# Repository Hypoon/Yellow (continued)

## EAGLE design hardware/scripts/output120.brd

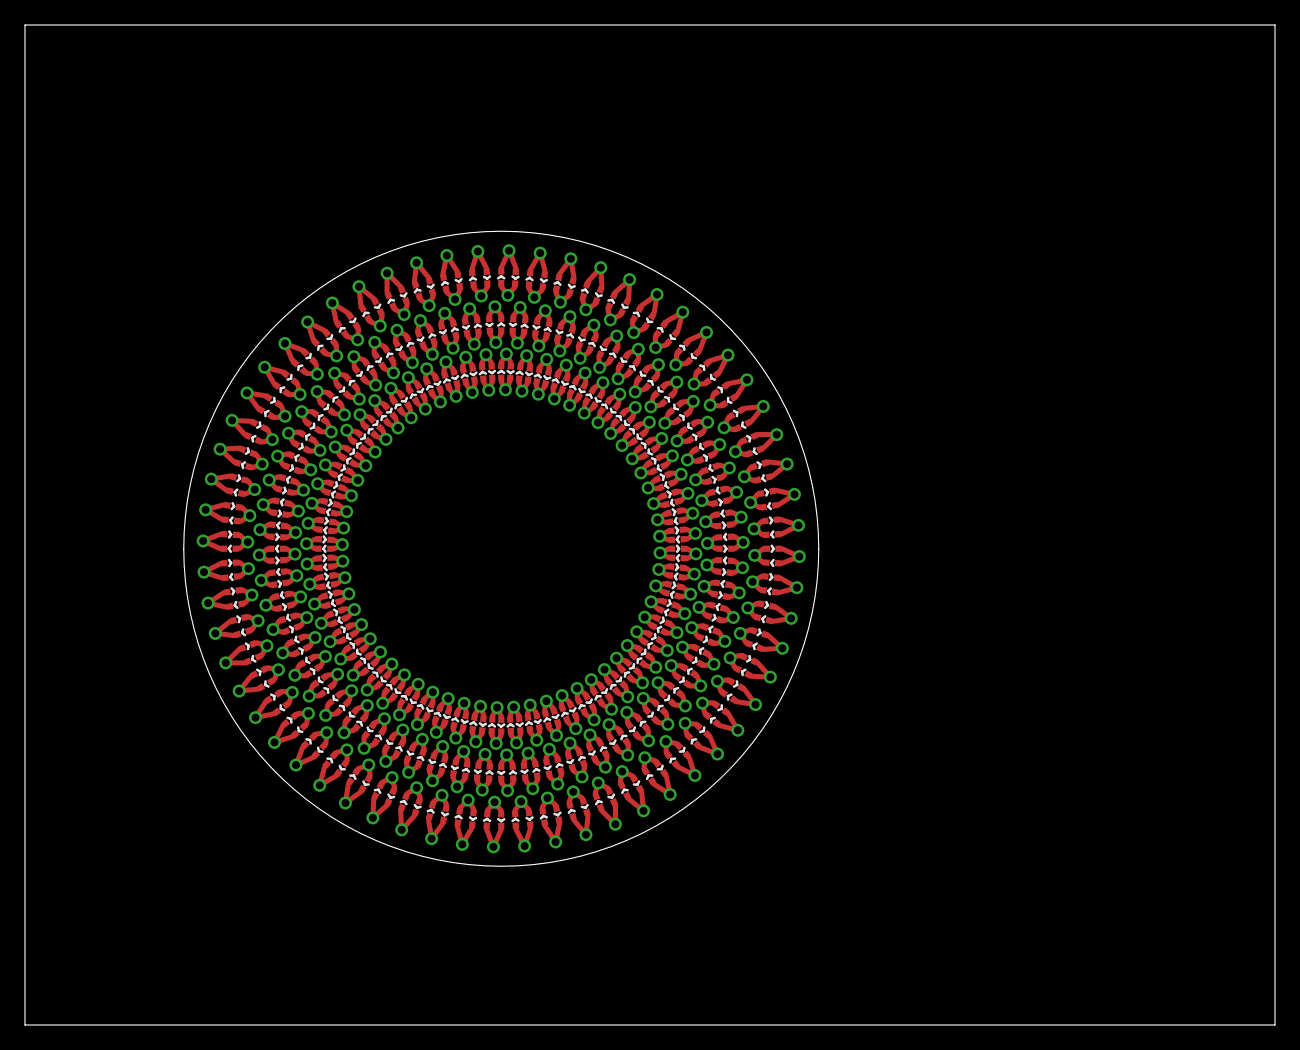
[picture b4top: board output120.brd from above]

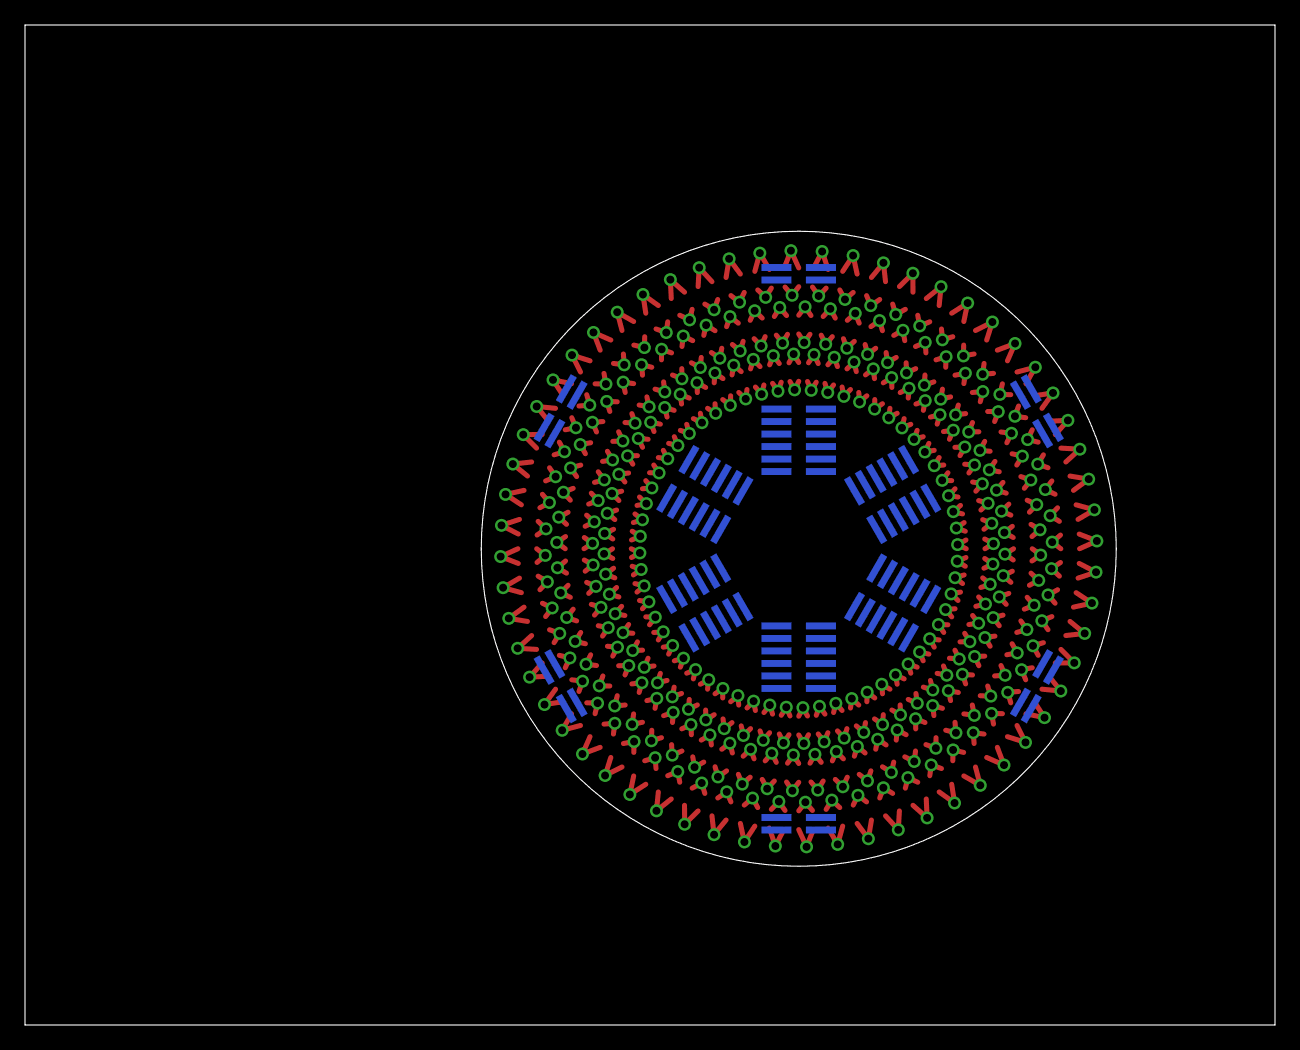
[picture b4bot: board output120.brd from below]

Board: 2 copper layers, 100.0 x 80.0 mm, 378 parts (18 on the bottom side), 360 nets.

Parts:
H1, H2, H3, H4, H5, H6, H7, H8, H9, H10, H11, H12: 2X3; 3X2_1MM_SMD
H13, H14, H15, H16, H17, H18: 2X2; 2X2_1MM_SMD
LED1, LED2, LED3, LED4, LED5, LED6, LED7, LED8, LED9, LED10, LED11, LED12, LED13, LED14, LED15, LED16, LED17, LED18, LED19, LED20, LED21, LED22, LED23, LED24, LED25, LED26, LED27, LED28, LED29, LED30, LED31, LED32, LED33, LED34, LED35, LED36, LED37, LED38, LED39, LED40, LED41, LED42, LED43, LED44, LED45, LED46, LED47, LED48, LED49, LED50, LED51, LED52, LED53, LED54, LED55, LED56, LED57, LED58, LED59, LED60, LED61, LED62, LED63, LED64, LED65, LED66, LED67, LED68, LED69, LED70, LED71, LED72, LED73, LED74, LED75, LED76, LED77, LED78, LED79, LED80, LED81, LED82, LED83, LED84, LED85, LED86, LED87, LED88, LED89, LED90, LED91, LED92, LED93, LED94, LED95, LED96, LED97, LED98, LED99, LED100, LED101, LED102, LED103, LED104, LED105, LED106, LED107, LED108, LED109, LED110, LED111, LED112, LED113, LED114, LED115, LED116, LED117, LED118, LED119, LED120: RED; LED-0402
LED121, LED122, LED123, LED124, LED125, LED126, LED127, LED128, LED129, LED130, LED131, LED132, LED133, LED134, LED135, LED136, LED137, LED138, LED139, LED140, LED141, LED142, LED143, LED144, LED145, LED146, LED147, LED148, LED149, LED150, LED151, LED152, LED153, LED154, LED155, LED156, LED157, LED158, LED159, LED160, LED161, LED162, LED163, LED164, LED165, LED166, LED167, LED168, LED169, LED170, LED171, LED172, LED173, LED174, LED175, LED176, LED177, LED178, LED179, LED180, LED181, LED182, LED183, LED184, LED185, LED186, LED187, LED188, LED189, LED190, LED191, LED192, LED193, LED194, LED195, LED196, LED197, LED198, LED199, LED200, LED201, LED202, LED203, LED204, LED205, LED206, LED207, LED208, LED209, LED210, LED211, LED212, LED213, LED214, LED215, LED216, LED217, LED218, LED219, LED220, LED221, LED222, LED223, LED224, LED225, LED226, LED227, LED228, LED229, LED230, LED231, LED232, LED233, LED234, LED235, LED236, LED237, LED238, LED239, LED240: GREEN; LED-0402
LED241, LED242, LED243, LED244, LED245, LED246, LED247, LED248, LED249, LED250, LED251, LED252, LED253, LED254, LED255, LED256, LED257, LED258, LED259, LED260, LED261, LED262, LED263, LED264, LED265, LED266, LED267, LED268, LED269, LED270, LED271, LED272, LED273, LED274, LED275, LED276, LED277, LED278, LED279, LED280, LED281, LED282, LED283, LED284, LED285, LED286, LED287, LED288, LED289, LED290, LED291, LED292, LED293, LED294, LED295, LED296, LED297, LED298, LED299, LED300, LED301, LED302, LED303, LED304, LED305, LED306, LED307, LED308, LED309, LED310, LED311, LED312, LED313, LED314, LED315, LED316, LED317, LED318, LED319, LED320, LED321, LED322, LED323, LED324, LED325, LED326, LED327, LED328, LED329, LED330, LED331, LED332, LED333, LED334, LED335, LED336, LED337, LED338, LED339, LED340, LED341, LED342, LED343, LED344, LED345, LED346, LED347, LED348, LED349, LED350, LED351, LED352, LED353, LED354, LED355, LED356, LED357, LED358, LED359, LED360: BLUE; LED-0402

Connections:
unnamed: LED1.A, LED2.C
unnamed: LED1.C, LED2.A
unnamed: LED3.A, LED4.C
unnamed: LED3.C, LED4.A
unnamed: LED5.A, LED6.C
unnamed: LED5.C, LED6.A
unnamed: LED7.A, LED8.C
unnamed: LED7.C, LED8.A
unnamed: LED9.A, LED10.C
unnamed: LED9.C, LED10.A
unnamed: LED11.A, LED12.C
unnamed: LED11.C, LED12.A
unnamed: LED13.A, LED14.C
unnamed: LED13.C, LED14.A
unnamed: LED15.A, LED16.C
unnamed: LED15.C, LED16.A
unnamed: LED17.A, LED18.C
unnamed: LED17.C, LED18.A
unnamed: LED19.A, LED20.C
unnamed: LED19.C, LED20.A
unnamed: LED21.A, LED22.C
unnamed: LED21.C, LED22.A
unnamed: LED23.A, LED24.C
unnamed: LED23.C, LED24.A
unnamed: LED25.A, LED26.C
unnamed: LED25.C, LED26.A
unnamed: LED27.A, LED28.C
unnamed: LED27.C, LED28.A
unnamed: LED29.A, LED30.C
unnamed: LED29.C, LED30.A
unnamed: LED31.A, LED32.C
unnamed: LED31.C, LED32.A
unnamed: LED33.A, LED34.C
unnamed: LED33.C, LED34.A
unnamed: LED35.A, LED36.C
unnamed: LED35.C, LED36.A
unnamed: LED37.A, LED38.C
unnamed: LED37.C, LED38.A
unnamed: LED39.A, LED40.C
unnamed: LED39.C, LED40.A
unnamed: LED41.A, LED42.C
unnamed: LED41.C, LED42.A
unnamed: LED43.A, LED44.C
unnamed: LED43.C, LED44.A
unnamed: LED45.A, LED46.C
unnamed: LED45.C, LED46.A
unnamed: LED47.A, LED48.C
unnamed: LED47.C, LED48.A
unnamed: LED49.A, LED50.C
unnamed: LED49.C, LED50.A
unnamed: LED51.A, LED52.C
unnamed: LED51.C, LED52.A
unnamed: LED53.A, LED54.C
unnamed: LED53.C, LED54.A
unnamed: LED55.A, LED56.C
unnamed: LED55.C, LED56.A
unnamed: LED57.A, LED58.C
unnamed: LED57.C, LED58.A
unnamed: LED59.A, LED60.C
unnamed: LED59.C, LED60.A
unnamed: LED61.A, LED62.C
unnamed: LED61.C, LED62.A
unnamed: LED63.A, LED64.C
unnamed: LED63.C, LED64.A
unnamed: LED65.A, LED66.C
unnamed: LED65.C, LED66.A
unnamed: LED67.A, LED68.C
unnamed: LED67.C, LED68.A
unnamed: LED69.A, LED70.C
unnamed: LED69.C, LED70.A
unnamed: LED71.A, LED72.C
unnamed: LED71.C, LED72.A
unnamed: LED73.A, LED74.C
unnamed: LED73.C, LED74.A
unnamed: LED75.A, LED76.C
unnamed: LED75.C, LED76.A
unnamed: LED77.A, LED78.C
unnamed: LED77.C, LED78.A
unnamed: LED79.A, LED80.C
unnamed: LED79.C, LED80.A
unnamed: LED81.A, LED82.C
unnamed: LED81.C, LED82.A
unnamed: LED83.A, LED84.C
unnamed: LED83.C, LED84.A
unnamed: LED85.A, LED86.C
unnamed: LED85.C, LED86.A
unnamed: LED87.A, LED88.C
unnamed: LED87.C, LED88.A
unnamed: LED89.A, LED90.C
unnamed: LED89.C, LED90.A
unnamed: LED91.A, LED92.C
unnamed: LED91.C, LED92.A
unnamed: LED93.A, LED94.C
unnamed: LED93.C, LED94.A
unnamed: LED95.A, LED96.C
unnamed: LED95.C, LED96.A
unnamed: LED97.A, LED98.C
unnamed: LED97.C, LED98.A
unnamed: LED99.A, LED100.C
unnamed: LED99.C, LED100.A
unnamed: LED101.A, LED102.C
unnamed: LED101.C, LED102.A
unnamed: LED103.A, LED104.C
unnamed: LED103.C, LED104.A
unnamed: LED105.A, LED106.C
unnamed: LED105.C, LED106.A
unnamed: LED107.A, LED108.C
unnamed: LED107.C, LED108.A
unnamed: LED109.A, LED110.C
unnamed: LED109.C, LED110.A
unnamed: LED111.A, LED112.C
unnamed: LED111.C, LED112.A
unnamed: LED113.A, LED114.C
unnamed: LED113.C, LED114.A
unnamed: LED115.A, LED116.C
unnamed: LED115.C, LED116.A
unnamed: LED117.A, LED118.C
unnamed: LED117.C, LED118.A
unnamed: LED119.A, LED120.C
unnamed: LED119.C, LED120.A
unnamed: LED122.C, LED123.A
unnamed: LED122.A, LED123.C
unnamed: LED124.C, LED125.A
unnamed: LED124.A, LED125.C
unnamed: LED126.C, LED127.A
unnamed: LED126.A, LED127.C
unnamed: LED128.C, LED129.A
unnamed: LED128.A, LED129.C
unnamed: LED130.C, LED131.A
unnamed: LED130.A, LED131.C
unnamed: LED132.C, LED133.A
unnamed: LED132.A, LED133.C
unnamed: LED134.C, LED135.A
unnamed: LED134.A, LED135.C
unnamed: LED136.C, LED137.A
unnamed: LED136.A, LED137.C
unnamed: LED138.C, LED139.A
unnamed: LED138.A, LED139.C
unnamed: LED140.C, LED141.A
unnamed: LED140.A, LED141.C
unnamed: LED142.C, LED143.A
unnamed: LED142.A, LED143.C
unnamed: LED144.C, LED145.A
unnamed: LED144.A, LED145.C
unnamed: LED146.C, LED147.A
unnamed: LED146.A, LED147.C
unnamed: LED148.C, LED149.A
unnamed: LED148.A, LED149.C
unnamed: LED150.C, LED151.A
unnamed: LED150.A, LED151.C
unnamed: LED152.C, LED153.A
unnamed: LED152.A, LED153.C
unnamed: LED154.C, LED155.A
unnamed: LED154.A, LED155.C
unnamed: LED156.C, LED157.A
unnamed: LED156.A, LED157.C
unnamed: LED158.C, LED159.A
unnamed: LED158.A, LED159.C
unnamed: LED160.C, LED161.A
unnamed: LED160.A, LED161.C
unnamed: LED162.C, LED163.A
unnamed: LED162.A, LED163.C
unnamed: LED164.C, LED165.A
unnamed: LED164.A, LED165.C
unnamed: LED166.C, LED167.A
unnamed: LED166.A, LED167.C
unnamed: LED168.C, LED169.A
unnamed: LED168.A, LED169.C
unnamed: LED170.C, LED171.A
unnamed: LED170.A, LED171.C
unnamed: LED172.C, LED173.A
unnamed: LED172.A, LED173.C
unnamed: LED174.C, LED175.A
unnamed: LED174.A, LED175.C
unnamed: LED176.C, LED177.A
unnamed: LED176.A, LED177.C
unnamed: LED178.C, LED179.A
unnamed: LED178.A, LED179.C
unnamed: LED180.C, LED181.A
unnamed: LED180.A, LED181.C
unnamed: LED182.C, LED183.A
unnamed: LED182.A, LED183.C
unnamed: LED184.C, LED185.A
unnamed: LED184.A, LED185.C
unnamed: LED186.C, LED187.A
unnamed: LED186.A, LED187.C
unnamed: LED188.C, LED189.A
unnamed: LED188.A, LED189.C
unnamed: LED190.C, LED191.A
unnamed: LED190.A, LED191.C
unnamed: LED192.C, LED193.A
unnamed: LED192.A, LED193.C
unnamed: LED194.C, LED195.A
unnamed: LED194.A, LED195.C
unnamed: LED196.C, LED197.A
unnamed: LED196.A, LED197.C
unnamed: LED198.C, LED199.A
unnamed: LED198.A, LED199.C
unnamed: LED200.C, LED201.A
unnamed: LED200.A, LED201.C
unnamed: LED202.C, LED203.A
unnamed: LED202.A, LED203.C
unnamed: LED204.C, LED205.A
unnamed: LED204.A, LED205.C
unnamed: LED206.C, LED207.A
unnamed: LED206.A, LED207.C
unnamed: LED208.C, LED209.A
unnamed: LED208.A, LED209.C
unnamed: LED210.C, LED211.A
unnamed: LED210.A, LED211.C
unnamed: LED212.C, LED213.A
unnamed: LED212.A, LED213.C
unnamed: LED214.C, LED215.A
unnamed: LED214.A, LED215.C
unnamed: LED216.C, LED217.A
unnamed: LED216.A, LED217.C
unnamed: LED218.C, LED219.A
unnamed: LED218.A, LED219.C
unnamed: LED220.C, LED221.A
unnamed: LED220.A, LED221.C
unnamed: LED222.C, LED223.A
unnamed: LED222.A, LED223.C
unnamed: LED224.C, LED225.A
unnamed: LED224.A, LED225.C
unnamed: LED226.C, LED227.A
unnamed: LED226.A, LED227.C
unnamed: LED228.C, LED229.A
unnamed: LED228.A, LED229.C
unnamed: LED230.C, LED231.A
unnamed: LED230.A, LED231.C
unnamed: LED232.C, LED233.A
unnamed: LED232.A, LED233.C
unnamed: LED234.C, LED235.A
unnamed: LED234.A, LED235.C
unnamed: LED236.C, LED237.A
unnamed: LED236.A, LED237.C
unnamed: LED238.C, LED239.A
unnamed: LED238.A, LED239.C
unnamed: LED121.A, LED240.C
unnamed: LED121.C, LED240.A
unnamed: LED241.A, LED242.C
unnamed: LED241.C, LED242.A
unnamed: LED243.A, LED244.C
unnamed: LED243.C, LED244.A
unnamed: LED245.A, LED246.C
unnamed: LED245.C, LED246.A
unnamed: LED247.A, LED248.C
unnamed: LED247.C, LED248.A
unnamed: LED249.A, LED250.C
unnamed: LED249.C, LED250.A
unnamed: LED251.A, LED252.C
unnamed: LED251.C, LED252.A
unnamed: LED253.A, LED254.C
unnamed: LED253.C, LED254.A
unnamed: LED255.A, LED256.C
unnamed: LED255.C, LED256.A
unnamed: LED257.A, LED258.C
unnamed: LED257.C, LED258.A
unnamed: LED259.A, LED260.C
unnamed: LED259.C, LED260.A
unnamed: LED261.A, LED262.C
unnamed: LED261.C, LED262.A
unnamed: LED263.A, LED264.C
unnamed: LED263.C, LED264.A
unnamed: LED265.A, LED266.C
unnamed: LED265.C, LED266.A
unnamed: LED267.A, LED268.C
unnamed: LED267.C, LED268.A
unnamed: LED269.A, LED270.C
unnamed: LED269.C, LED270.A
unnamed: LED271.A, LED272.C
unnamed: LED271.C, LED272.A
unnamed: LED273.A, LED274.C
unnamed: LED273.C, LED274.A
unnamed: LED275.A, LED276.C
unnamed: LED275.C, LED276.A
unnamed: LED277.A, LED278.C
unnamed: LED277.C, LED278.A
unnamed: LED279.A, LED280.C
unnamed: LED279.C, LED280.A
unnamed: LED281.A, LED282.C
unnamed: LED281.C, LED282.A
unnamed: LED283.A, LED284.C
unnamed: LED283.C, LED284.A
unnamed: LED285.A, LED286.C
unnamed: LED285.C, LED286.A
unnamed: LED287.A, LED288.C
unnamed: LED287.C, LED288.A
unnamed: LED289.A, LED290.C
unnamed: LED289.C, LED290.A
unnamed: LED291.A, LED292.C
unnamed: LED291.C, LED292.A
unnamed: LED293.A, LED294.C
unnamed: LED293.C, LED294.A
unnamed: LED295.A, LED296.C
unnamed: LED295.C, LED296.A
unnamed: LED297.A, LED298.C
unnamed: LED297.C, LED298.A
unnamed: LED299.A, LED300.C
unnamed: LED299.C, LED300.A
unnamed: LED301.A, LED302.C
unnamed: LED301.C, LED302.A
unnamed: LED303.A, LED304.C
unnamed: LED303.C, LED304.A
unnamed: LED305.A, LED306.C
unnamed: LED305.C, LED306.A
unnamed: LED307.A, LED308.C
unnamed: LED307.C, LED308.A
unnamed: LED309.A, LED310.C
unnamed: LED309.C, LED310.A
unnamed: LED311.A, LED312.C
unnamed: LED311.C, LED312.A
unnamed: LED313.A, LED314.C
unnamed: LED313.C, LED314.A
unnamed: LED315.A, LED316.C
unnamed: LED315.C, LED316.A
unnamed: LED317.A, LED318.C
unnamed: LED317.C, LED318.A
unnamed: LED319.A, LED320.C
unnamed: LED319.C, LED320.A
unnamed: LED321.A, LED322.C
unnamed: LED321.C, LED322.A
unnamed: LED323.A, LED324.C
unnamed: LED323.C, LED324.A
unnamed: LED325.A, LED326.C
unnamed: LED325.C, LED326.A
unnamed: LED327.A, LED328.C
unnamed: LED327.C, LED328.A
unnamed: LED329.A, LED330.C
unnamed: LED329.C, LED330.A
unnamed: LED331.A, LED332.C
unnamed: LED331.C, LED332.A
unnamed: LED333.A, LED334.C
unnamed: LED333.C, LED334.A
unnamed: LED335.A, LED336.C
unnamed: LED335.C, LED336.A
unnamed: LED337.A, LED338.C
unnamed: LED337.C, LED338.A
unnamed: LED339.A, LED340.C
unnamed: LED339.C, LED340.A
unnamed: LED341.A, LED342.C
unnamed: LED341.C, LED342.A
unnamed: LED343.A, LED344.C
unnamed: LED343.C, LED344.A
unnamed: LED345.A, LED346.C
unnamed: LED345.C, LED346.A
unnamed: LED347.A, LED348.C
unnamed: LED347.C, LED348.A
unnamed: LED349.A, LED350.C
unnamed: LED349.C, LED350.A
unnamed: LED351.A, LED352.C
unnamed: LED351.C, LED352.A
unnamed: LED353.A, LED354.C
unnamed: LED353.C, LED354.A
unnamed: LED355.A, LED356.C
unnamed: LED355.C, LED356.A
unnamed: LED357.A, LED358.C
unnamed: LED357.C, LED358.A
unnamed: LED359.A, LED360.C
unnamed: LED359.C, LED360.A

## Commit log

2012-08-13 Upload of existing files
2012-08-13 Reorganization
2012-08-13 GitIgnore Update
2012-08-13 Removing old saves from repo
2012-08-13 Updated gitignore
2012-08-13 Removing OS files
2012-08-13 Removing more OS Files
2012-08-13 Updated .gitignore
2012-08-13 update gitignore for "old" folder
2012-08-15 Added LED to library
2012-08-15 Removing old versions
2012-08-15 Upload of current versions
2012-08-15 Variation of eagle.epf
2012-08-16 Removing dependence on Sparkfun-LED
2012-08-16 Finished eliminating dependencies on other libraries.
2012-08-16 Created common boilerplate code files
2012-08-16 removed german description from designrules.brd
    Extended character sets were causing problems, it is suspected that
    these problems may be able to be resolved by changing the encoding of
    the XML document.
2012-08-16 eagle's project file is doing it's thing...
2012-08-16 upload of new script and resulting output
2012-08-16 project file doing its thing...
2012-08-18 Huge update: added elements, added front-side signals.
    Removed offset variables in favor of variables representing the center
    of the figure.
    User variables written as inches multiplied by 25.4.
    Added variables for element ring locations, both for LEDs and headers.
    Removed commented code that has already been re-implemented in a
    superior way.
2012-08-18 Added one-liner enabling python to be run implicitly.
2012-08-18 Refactored element positioning code into a new function.
2012-08-18 Revised refactoring to be more element-universal
2012-08-18 Factored out a function for separate processing of pseudo-polar coordinates.
2012-08-18 frompolar and addelementoncircle now assume centerx and centery to be ORIGINX and ORIGINY if not specified.
2012-08-18 Forgotten update to addelementoncircle
    Meant to be included in last commit
2012-08-18 started refactoring code using the frompolar function (1/3 done)
2012-08-20 Finished refactoring code using the frompolar function.
2012-08-20 Created elementring function and factored out relevant code.
2012-08-20 Ignoring eagle.epf from now on, made some minor revisions to elementring, and did some minor whitespace cleanup.
2012-08-20 Factored out creation of rings of LEDs, with signals and vias, into separate functions ledring and ledring2.
2012-08-21 Removed dependence on "Imaginary rings" for via placement.
    Also changed middle and outer rings from being defined to being
    calculated.
2012-08-21 Script and output modified minimally for a 120-tick setup.
2012-08-21 Added 0402 LED to library
2012-08-21 Updated files to include updated library.
2012-08-21 Ideas to play with, ignore these for now.
2012-08-21 Reorganized and cleaned up old attempts into a new folder.
2012-08-21 More cleanup and reorganization of old attempts
2012-08-21 Change in net names from previous revisions!
    This way makes more sense. The nets are the same, but simply numbered
    in a different order.
2013-03-21 Created a firmware directory (currently empty)
